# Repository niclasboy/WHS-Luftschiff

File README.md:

# WHS-Luftschiff

Dieses Projekt dokumentiert den Bau eines Starrluftschiffes im Rahmen des Studienganges Elektrotechnik an der Westfälischen Hochschule Gelsenkirchen.

# Mechanik / Aufbau Luftschiff

Dass Luftschiff wird durch vier Motoren angetriebe. Die Motoren sind an Propellergondeln montiert. So lassen die Motoren um -+90° im Bezug zur Hauptachse bewegen. Dank der Motoren ist der Einsatz eines Leitwerkes nicht erforderlich, da die hinteren zwei Motoren diese Aufgabe übernehmen können. Auch können alle Motoren senkrecht zum Luftschiff geneigt werden(90°). Dies kann dazu genutzt werden, um den Auftrieb zu erhöhen bzw. zu verringen. Im Falle eines Ausfalls der Funkverbindung können so die Motoren automatisch senkrecht zum Luftschiff geneigt werden, um das Luftschiff zum sinken zu "zwingen". 

Das Luftschiff besteht aus einem Holzgerippe, welches mit einer dünnen Folie luftdicht verschlossen ist. Um die dichtigkeit weiter zu steigen, beinhaltet das Luftschiff einen innen Körper, welcher später mit Helium/Ballongas gefüllt wird. Dies hat zusätlcih den Vorteil, dass sich im Luftschiff reines Helium befindet.

# Elektronik / Flugsteuerung

https://github.com/niclasboy/Flugsteuerung

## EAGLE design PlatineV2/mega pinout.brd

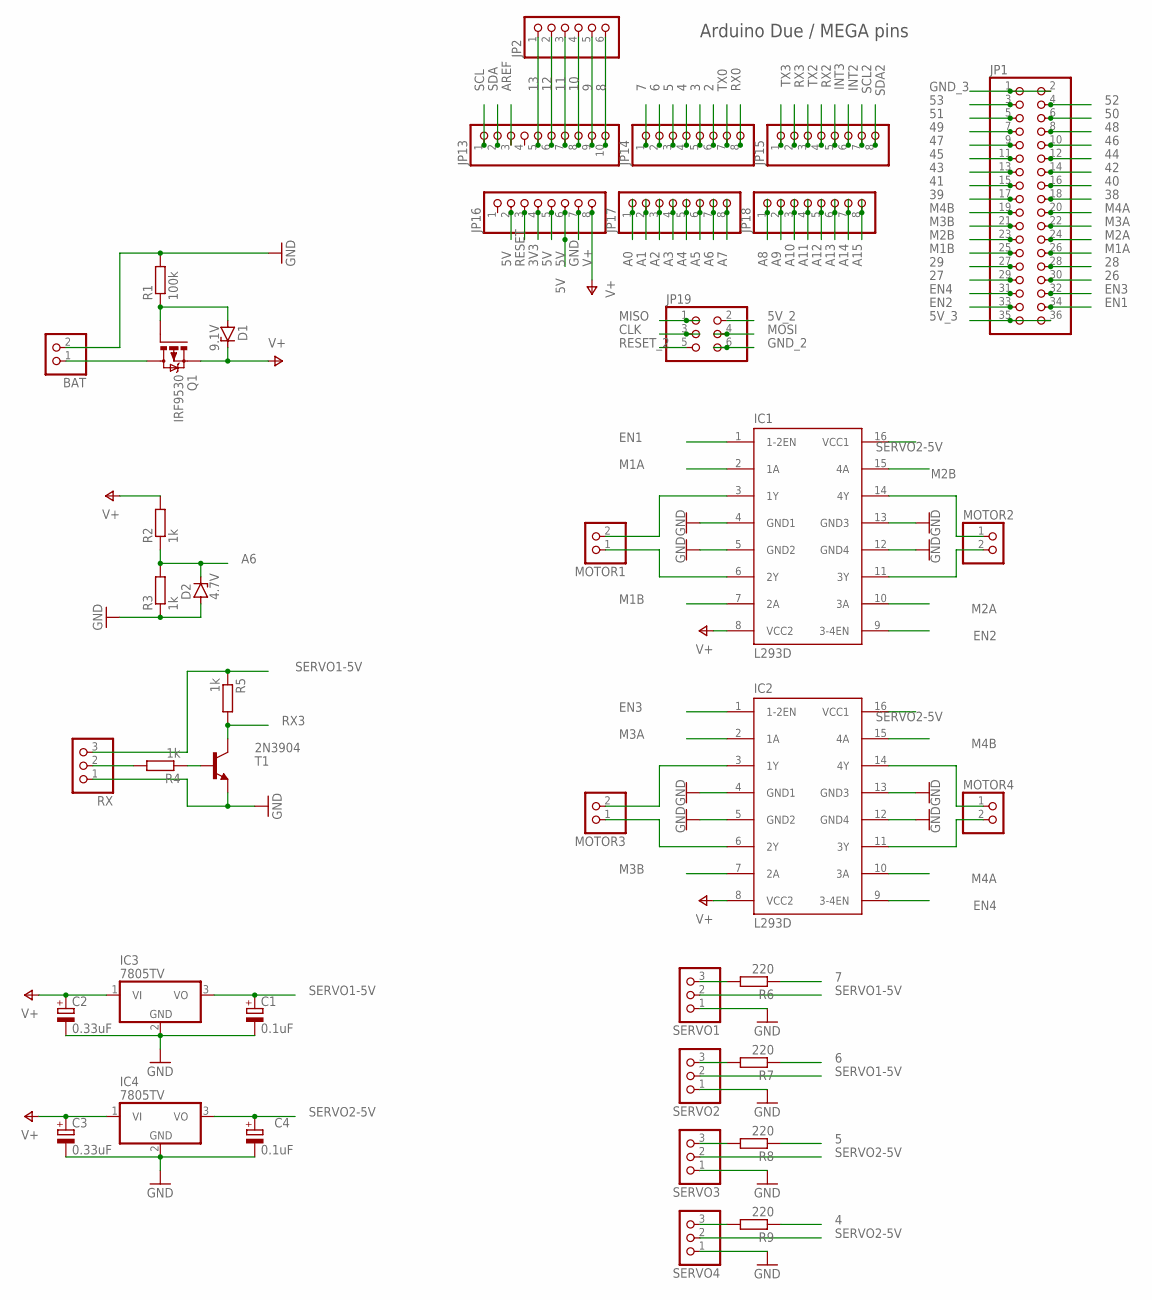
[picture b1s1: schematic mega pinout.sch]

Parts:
BAT: PINHD-1X2; 1X02
C1, C4: 0.1uF; E2,5-7
C2, C3: 0.33uF; E2,5-7
D1: 9.1V; ZDIO-2.5
D2: 4.7V; ZDIO-2.5
IC1, IC2: L293D; DIL16
IC3, IC4: 7805TV; TO220V
JP1: PINHD-2X18; 2X18
JP2: PINHD-1X6; 1X06
JP13: PINHD-1X10; 1X10
JP14, JP15, JP16, JP17, JP18: PINHD-1X8; 1X08
JP19: PINHD-2X3; 2X03
MOTOR1, MOTOR2, MOTOR3, MOTOR4: PINHD-1X2; 1X02
Q1: IRF9530; TO220BV
R1: 100k; 0207/2V
R2, R3, R4, R5: 1k; 0207/2V
R6, R7, R8, R9: 220; 0207/2V
RX: PINHD-1X3; 1X03
SERVO1, SERVO2, SERVO3, SERVO4: PINHD-1X3; 1X03
T1: 2N3904; TO92

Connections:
2: JP14.6
3: JP14.5
3V3: JP16.4
4: JP14.4, R9.1
5: JP14.3, R8.1
5V: JP16.2, JP16.5, JP16.6
5V_2: JP19.2
5V_3: JP1.35, JP1.36
6: JP14.2, R7.1
7: JP14.1, R6.1
8: JP2.6, JP13.10
9: JP2.5, JP13.9
10: JP2.4, JP13.8
11: JP2.3, JP13.7
12: JP2.2, JP13.6
13: JP2.1, JP13.5
26: JP1.30
27: JP1.29
28: JP1.28
29: JP1.27
38: JP1.18
39: JP1.17
40: JP1.16
41: JP1.15
42: JP1.14
43: JP1.13
44: JP1.12
45: JP1.11
46: JP1.10
47: JP1.9
48: JP1.8
49: JP1.7
50: JP1.6
51: JP1.5
52: JP1.4
53: JP1.3
A0: JP17.1
A1: JP17.2
A2: JP17.3
A3: JP17.4
A4: JP17.5
A5: JP17.6
A6: D2.C, JP17.7, R2.1, R3.2
A7: JP17.8
A8: JP18.1
A9: JP18.2
A10: JP18.3
A11: JP18.4
A12: JP18.5
A13: JP18.6
A14: JP18.7
A15: JP18.8
AREF: JP13.3
CLK: JP19.3
EN1: IC1.1 (1-2EN), JP1.34
EN2: IC1.9 (3-4EN), JP1.33
EN3: IC2.1 (1-2EN), JP1.32
EN4: IC2.9 (3-4EN), JP1.31
GND: BAT.2, C1.-, C2.-, C3.-, C4.-, D2.A, IC1.4 (GND1), IC1.5 (GND2), IC1.12 (GND4), IC1.13 (GND3), IC2.4 (GND1), IC2.12 (GND4), IC3.2 (GND), IC4.2 (GND), JP16.7, R1.2, R3.1, RX.1, SERVO1.1, SERVO2.1, SERVO3.1, SERVO4.1, T1.3 (E)
GND_2: JP19.6
GND_3: JP1.1, JP1.2
INT2: JP15.6
INT3: JP15.5
M1A: IC1.2 (1A), JP1.26
M1B: IC1.7 (2A), JP1.25
M2A: IC1.10 (3A), JP1.24
M2B: IC1.15 (4A), JP1.23
M3A: IC2.2 (1A), JP1.22
M3B: IC2.7 (2A), JP1.21
M4A: IC2.10 (3A), JP1.20
M4B: IC2.15 (4A), JP1.19
MISO: JP19.1
MOSI: JP19.4
MOTOR3: IC2.6 (2Y), MOTOR3.1
unnamed: IC1.3 (1Y), MOTOR1.2
unnamed: IC1.6 (2Y), MOTOR1.1
unnamed: IC1.11 (3Y), MOTOR2.2
unnamed: IC1.14 (4Y), MOTOR2.1
unnamed: IC2.3 (1Y), MOTOR3.2
unnamed: R4.2, RX.2
unnamed: IC2.11 (3Y), MOTOR4.2
unnamed: IC2.14 (4Y), MOTOR4.1
unnamed: BAT.1, Q1.D
unnamed: D1.A, Q1.G, R1.1
unnamed: R4.1, T1.2 (B)
unnamed: R7.2, SERVO2.3
unnamed: R6.2, SERVO1.3
unnamed: R8.2, SERVO3.3
unnamed: R9.2, SERVO4.3
RESET: JP16.3
RESET_2: JP19.5
RX0: JP14.8
RX2: JP15.4
RX3: JP15.2, R5.2, T1.1 (C)
SCL: JP13.1
SCL2: JP15.7
SDA: JP13.2
SDA2: JP15.8
SERVO1-5V: C1.+, IC3.3 (VO), R5.1, RX.3, SERVO1.2, SERVO2.2
SERVO2-5V: C4.+, IC1.16 (VCC1), IC2.16 (VCC1), IC4.3 (VO), SERVO3.2, SERVO4.2
TX0: JP14.7
TX2: JP15.3
TX3: JP15.1
V+: C2.+, C3.+, D1.C, IC1.8 (VCC2), IC2.8 (VCC2), IC3.1 (VI), IC4.1 (VI), JP16.8, Q1.S, R2.2

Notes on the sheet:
Arduino Due / MEGA pins

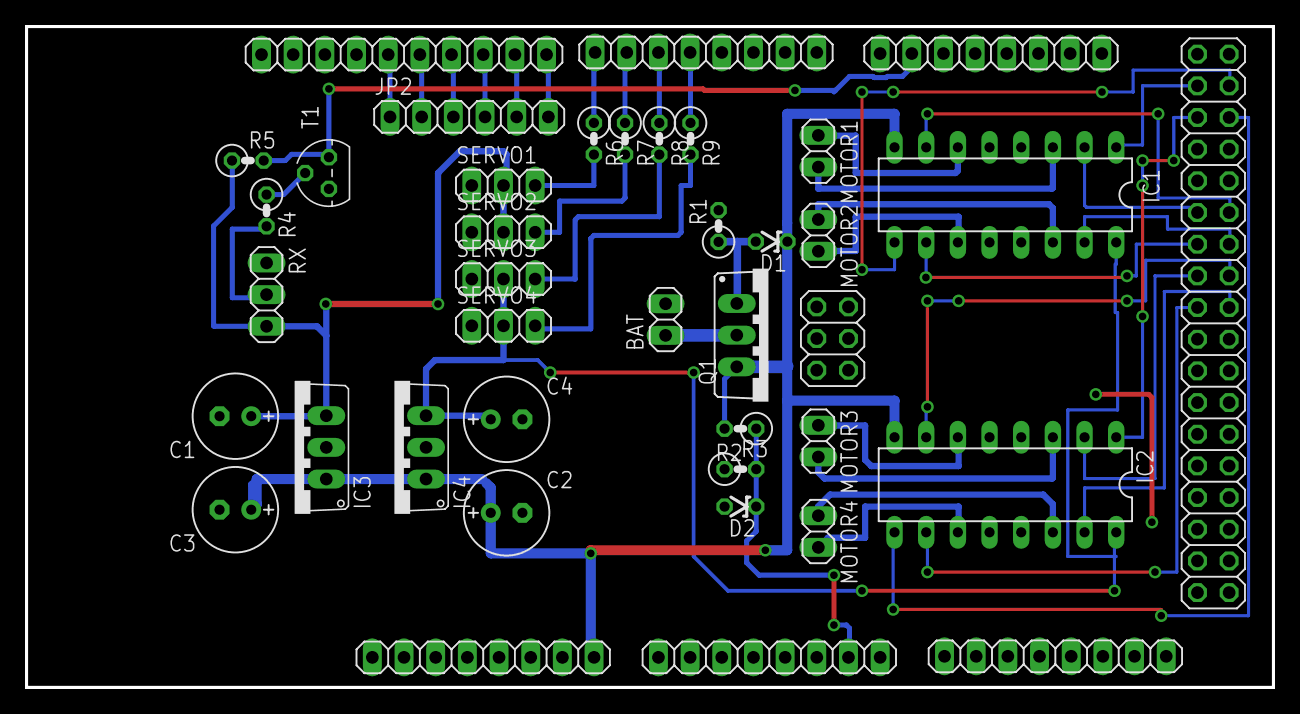
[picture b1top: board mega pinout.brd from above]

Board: 2 copper layers, 100.0 x 53.0 mm, 40 parts (0 on the bottom side), 47 nets.

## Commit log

2021-10-18 Create Mechanik
2021-10-18 Create Avionik
2021-11-17 Erste Schritte vom Platinenlayout
2021-11-19 Delete Elektronik directory
    Befinden sich in extra repo

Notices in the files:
parts and their libraries:
SparkFun-PowerSymbols: Licensing: Creative Commons ShareAlike 4.0 International - https://creativecommons.org/licenses/by-sa/4.0
